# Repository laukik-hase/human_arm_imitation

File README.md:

# Imitation of Human Arm using a 5-DoF Manipulator

<!-- TABLE OF CONTENTS -->

## Table of Contents

- [Imitation of Human Arm using a 5-DoF Manipulator](#imitation-of-human-arm-using-a-5-dof-manipulator)
  - [Table of Contents](#table-of-contents)
  - [About The Project](#about-the-project)
  - [Contributors](#contributors)
  - [Resources](#resources)
  - [Acknowledgements](#acknowledgements)
  - [License](#license)

<!-- ABOUT THE PROJECT -->

## About The Project

- The project aims at develop a 5-DoF manipulator capable of precise imitation of the human arm. The manipulator will be tested in a simulated environment and then implemented in reality.

- The first challenge is to track the position of human joints and acquire joint parameters data.
A motion-capture system consisting of IMU sensors attached to the human arm will be used for the purpose.

- The next challenge is to map the motion of the human to the manipulator, with kinematic and dynamic
modeling of the manipulator for precise and accurate control.

- After establishing a stable system for arm imitation, it will be tested on applications like pick-and-place and tracing a curve.

- Everything about the project: reports, progress, demos (photos and videos) can be found [here](https://drive.google.com/drive/folders/1VRj0Rsg3wywi9sTcepC8vw8A19dxCz2f?usp=sharing).

- For detailed description of the project, view this [report](human_arm_imitation.pdf).

## Contributors

* [Vishnuparammal](https://github.com/Vishnuparammal)
* [ved29](https://github.com/ved29)
* [laukik-hase](https://github.com/laukik-hase)
* [ameya-apte](https://github.com/ameya-apte)

<!-- Acknowledgements and Resources-->

## Resources
- [Concept Development Report](https://drive.google.com/drive/folders/1PC-iJiLeUT0hi6oHv0CTknUYlQUyzkWc?usp=sharing)
- [Progress Status](https://drive.google.com/drive/folders/1OLMFB2oo_8WZqaWDnTHkVBi_Prd8paOJ?usp=sharing)
- [References](https://drive.google.com/drive/folders/1Bxyq7_aq28y-IdtfYdROcifC5CevMQnE?usp=sharing)
## Acknowledgements

- [AVITRA : 2019-2020](https://github.com/SRA-AVITRA)
- [AVITRA : 2018-2019](https://github.com/atharvkhadtare/fyp_ws)
- [AVITRA : 2017-2018](https://github.com/sachin0x18/Imitation)

<!-- LICENSE -->

## License

Distributed under the MIT License. See `LICENSE` for more information.

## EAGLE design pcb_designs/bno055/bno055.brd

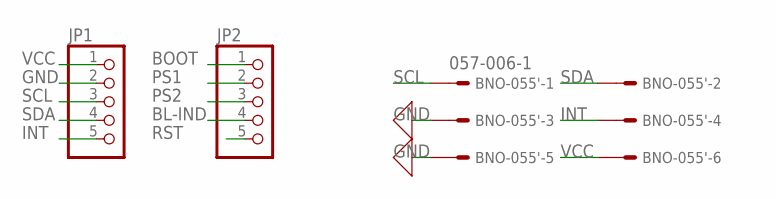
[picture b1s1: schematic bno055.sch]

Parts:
BNO-055': 057-006-1
JP1, JP2: PINHD-1X5; 1X05

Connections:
BL-IND: JP2.4
BOOT: JP2.1
GND: BNO-055'.3, BNO-055'.5, JP1.2
INT: BNO-055'.4, JP1.5
PS1: JP2.2
PS2: JP2.3
RST: JP2.5
SCL: BNO-055'.1, JP1.3
SDA: BNO-055'.2, JP1.4
VCC: BNO-055'.6, JP1.1

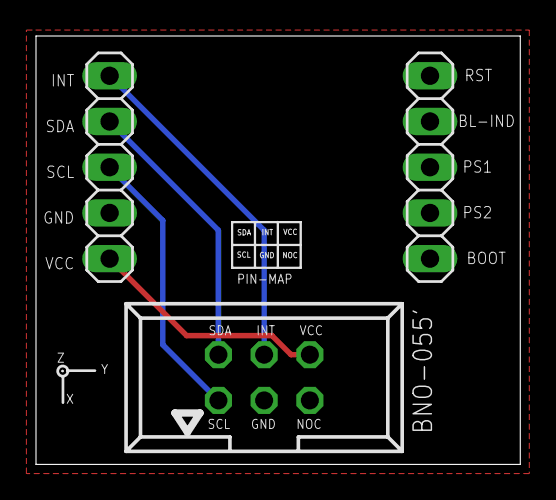
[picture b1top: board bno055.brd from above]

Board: 2 copper layers, 26.9 x 23.8 mm, 3 parts (0 on the bottom side), 5 nets.

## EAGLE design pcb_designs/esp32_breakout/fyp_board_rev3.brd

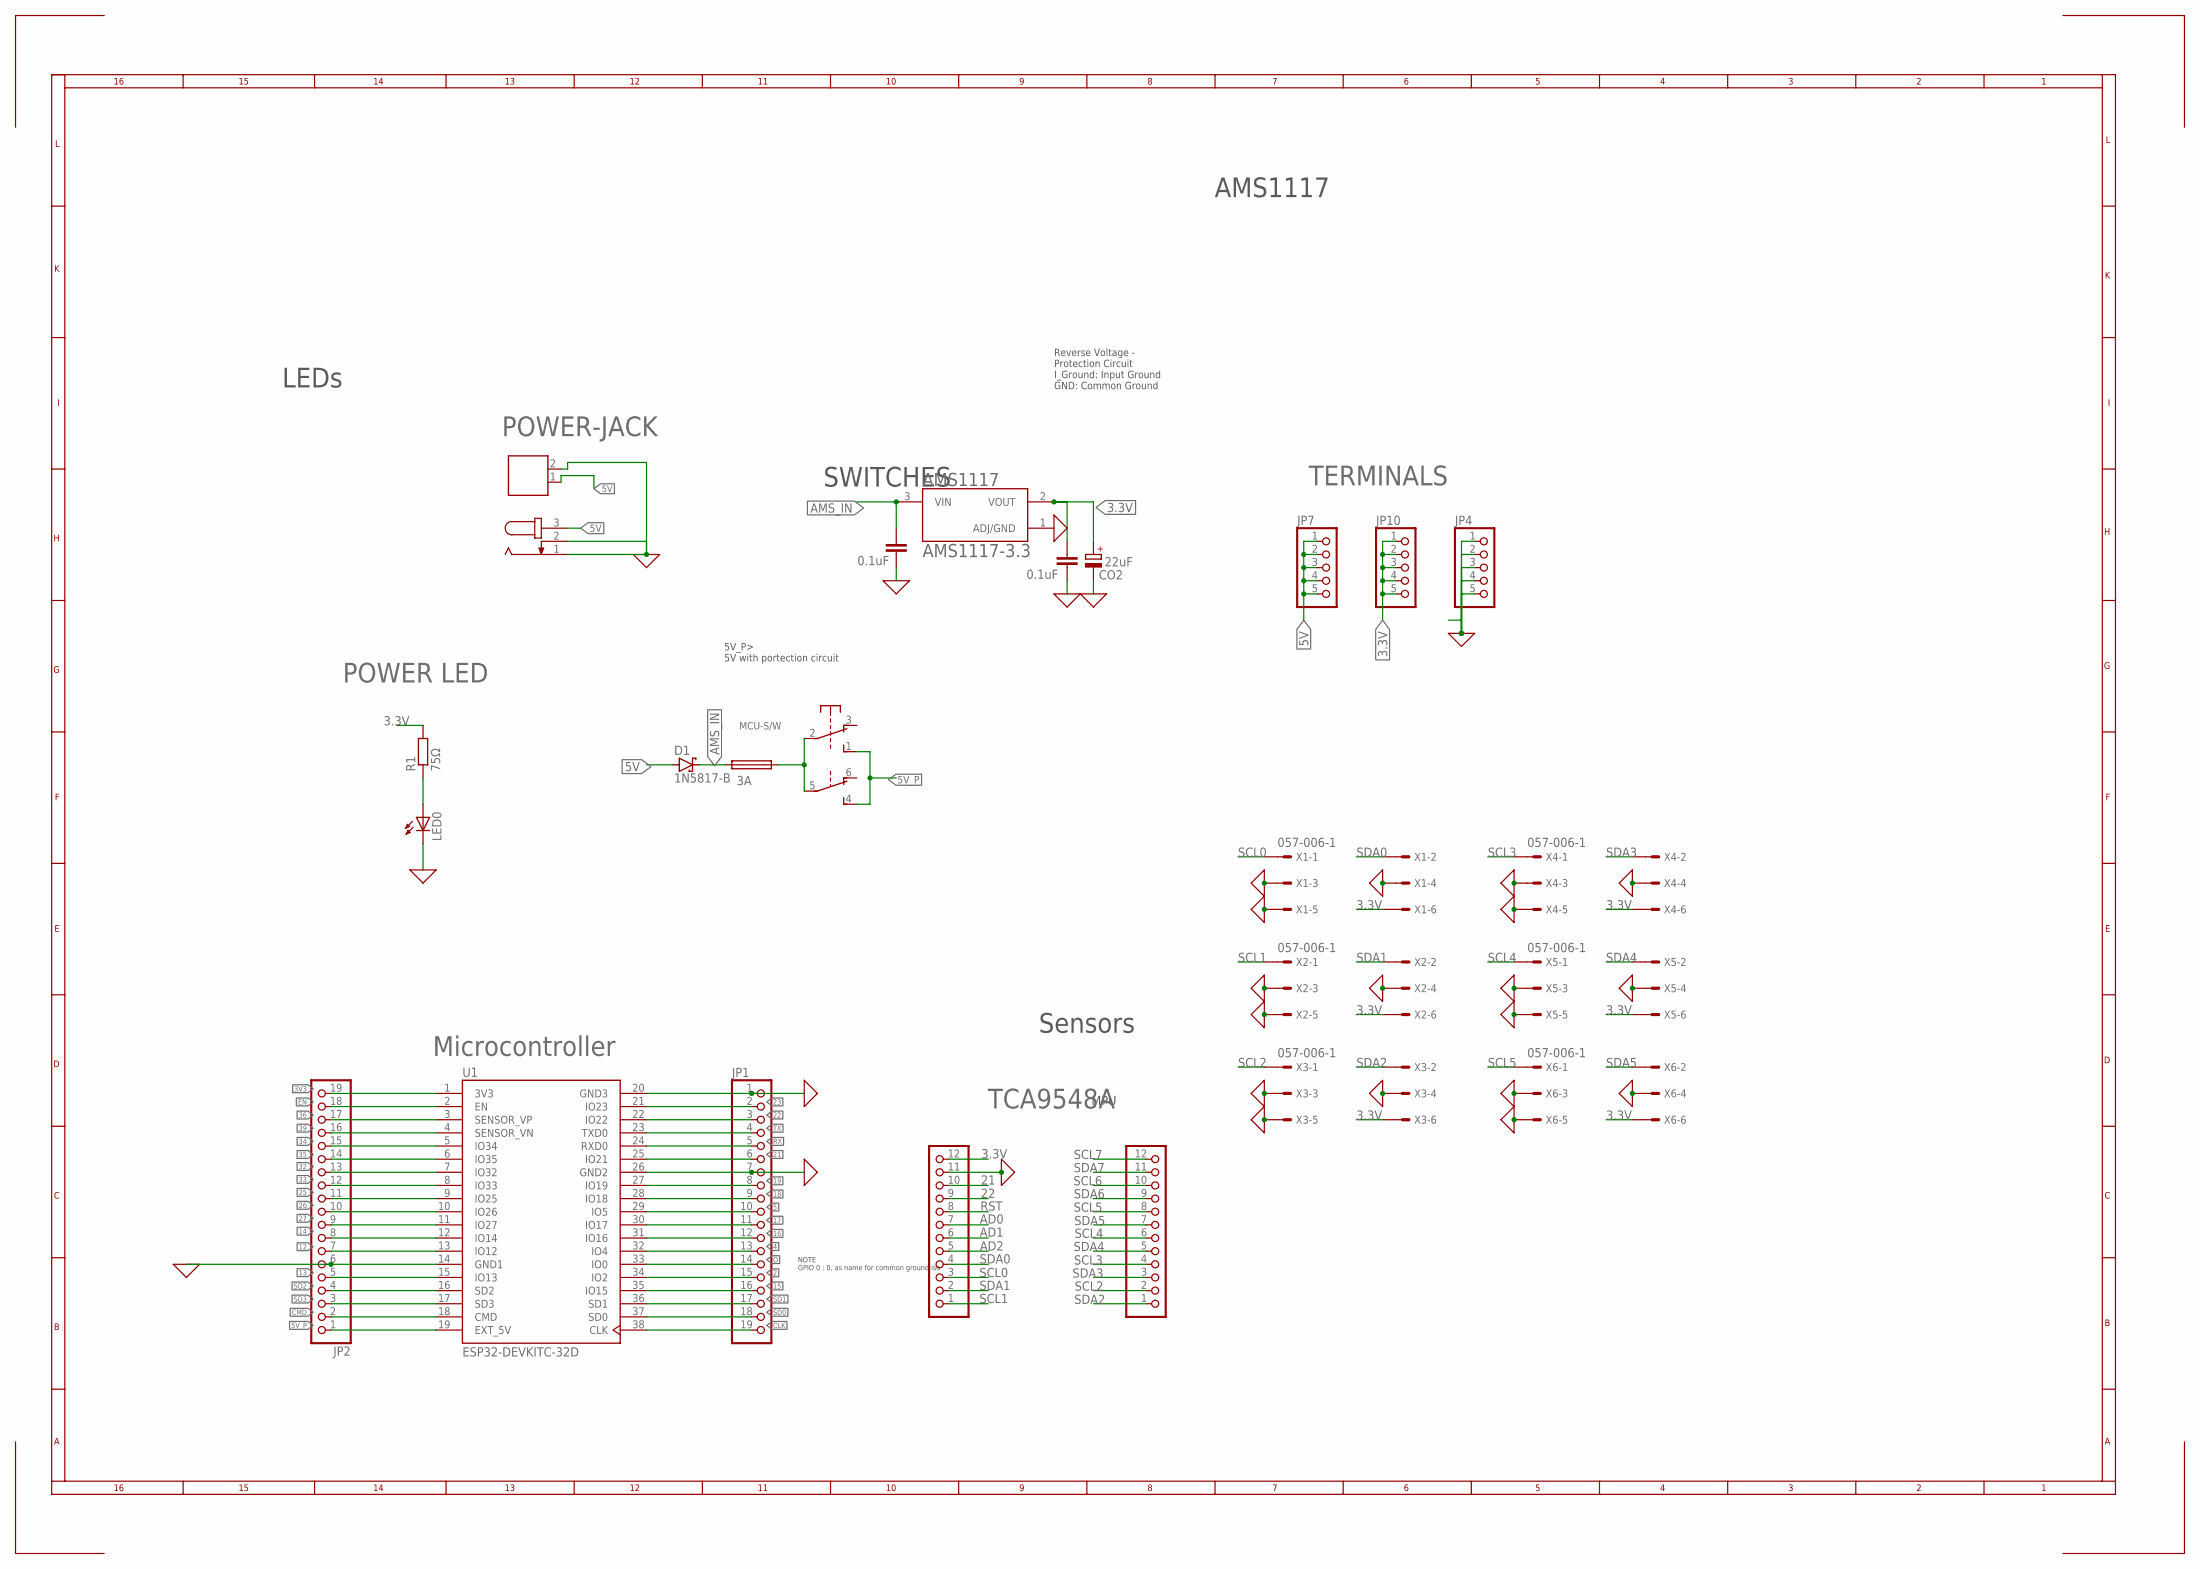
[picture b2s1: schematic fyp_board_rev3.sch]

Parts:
12V: 691131710002
AMS1117: AMS1117-3.3; SOT229P700X180-4N
CIN1: 0.1uF; C5B2.5
CO1: 0.1uF; C5B2.5
CO2: 22uF; E2,5-6
D1: 1N5817-B; DO41-7.6
F2: 3A; SH25
JP1, JP2: PINHD-1X19; 1X19
JP4, JP7, JP10: PINHD-1X5; 1X05
LED0: LED3MM
MCU-S/W: 9077-2
POWER-JACK: JACK-PLUG1; SPC4078
R1: 75Ω; 0207/10
SV2: PINHD-1X12; 1X12
TCA9548: PINHD-1X12; 1X12
U1: ESP32-DEVKITC-32D; MODULE_ESP32-DEVKITC-32D
X1, X2, X3, X4, X5, X6: 057-006-1

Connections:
0: 12V.2, AMS1117.1 (ADJ/GND), CIN1.1, CO1.1, CO2.-, JP1.1, JP1.7, JP2.6, JP4.1, JP4.2, JP4.3, JP4.4, JP4.5, LED0.K (C), POWER-JACK.1, POWER-JACK.2, TCA9548.11, U1.14 (GND1), U1.20 (GND3), U1.26 (GND2), X1.3, X1.4, X1.5, X2.3, X2.4, X2.5, X3.3, X3.4, X3.5, X4.3, X4.4, X4.5, X5.3, X5.4, X5.5, X6.3, X6.4, X6.5
2: JP1.15, U1.34 (IO2)
3.3V: AMS1117.2 (VOUT), CO1.2, CO2.+, JP10.1, JP10.2, JP10.3, JP10.4, JP10.5, R1.2, TCA9548.12, X1.6, X2.6, X3.6, X4.6, X5.6, X6.6
3V3: JP2.19, U1.1 (3V3)
4: JP1.13, U1.32 (IO4)
5: JP1.10, U1.29 (IO5)
5V: 12V.1, D1.A, JP7.1, JP7.2, JP7.3, JP7.4, JP7.5, POWER-JACK.3
5V_P: JP2.1, MCU-S/W.1 (S), MCU-S/W.4 (S), U1.19 (EXT_5V)
5_AF: F2.1, MCU-S/W.2, MCU-S/W.5
12: JP2.7, U1.13 (IO12)
13: JP2.5, U1.15 (IO13)
14: JP2.8, U1.12 (IO14)
15: JP1.16, U1.35 (IO15)
16: JP1.12, U1.31 (IO16)
17: JP1.11, U1.30 (IO17)
18: JP1.9, U1.28 (IO18)
19: JP1.8, U1.27 (IO19)
21: JP1.6, TCA9548.10, U1.25 (IO21)
22: JP1.3, TCA9548.9, U1.22 (IO22)
23: JP1.2, U1.21 (IO23)
25: JP2.11, U1.9 (IO25)
26: JP2.10, U1.10 (IO26)
27: JP2.9, U1.11 (IO27)
32: JP2.13, U1.7 (IO32)
33: JP2.12, U1.8 (IO33)
34: JP2.15, U1.5 (IO34)
35: JP2.14, U1.6 (IO35)
36: JP2.17, U1.3 (SENSOR_VP)
39: JP2.16, U1.4 (SENSOR_VN)
AD0: TCA9548.7
AD1: TCA9548.6
AD2: TCA9548.5
AMS_IN: AMS1117.3 (VIN), CIN1.2, D1.C, F2.2
CLK: JP1.19, U1.38 (CLK)
CMD: JP2.2, U1.18 (CMD)
EN: JP2.18, U1.2 (EN)
unnamed: LED0.A, R1.1
O: JP1.14, U1.33 (IO0)
RST: TCA9548.8
RX: JP1.5, U1.24 (RXD0)
SCL0: TCA9548.3, X1.1
SCL1: TCA9548.1, X2.1
SCL2: SV2.2, X3.1
SCL3: SV2.4, X4.1
SCL4: SV2.6, X5.1
SCL5: SV2.8, X6.1
SCL6: SV2.10
SCL7: SV2.12
SD0: JP1.18, U1.37 (SD0)
SD1: JP1.17, U1.36 (SD1)
SD2: JP2.4, U1.16 (SD2)
SD3: JP2.3, U1.17 (SD3)
SDA0: TCA9548.4, X1.2
SDA1: TCA9548.2, X2.2
SDA2: SV2.1, X3.2
SDA3: SV2.3, X4.2
SDA4: SV2.5, X5.2
SDA5: SV2.7, X6.2
SDA6: SV2.9
SDA7: SV2.11
TX: JP1.4, U1.23 (TXD0)

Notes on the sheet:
TERMINALS
Microcontroller
Reverse Voltage - Protection Circuit I_Ground: Input Ground GND: Common Ground
SWITCHES
5V_P> 5V with portection circuit
Sensors
MPU
NOTE GPIO 0 : 0, as name for common ground iso
AMS1117
LEDs
TCA9548A
POWER LED

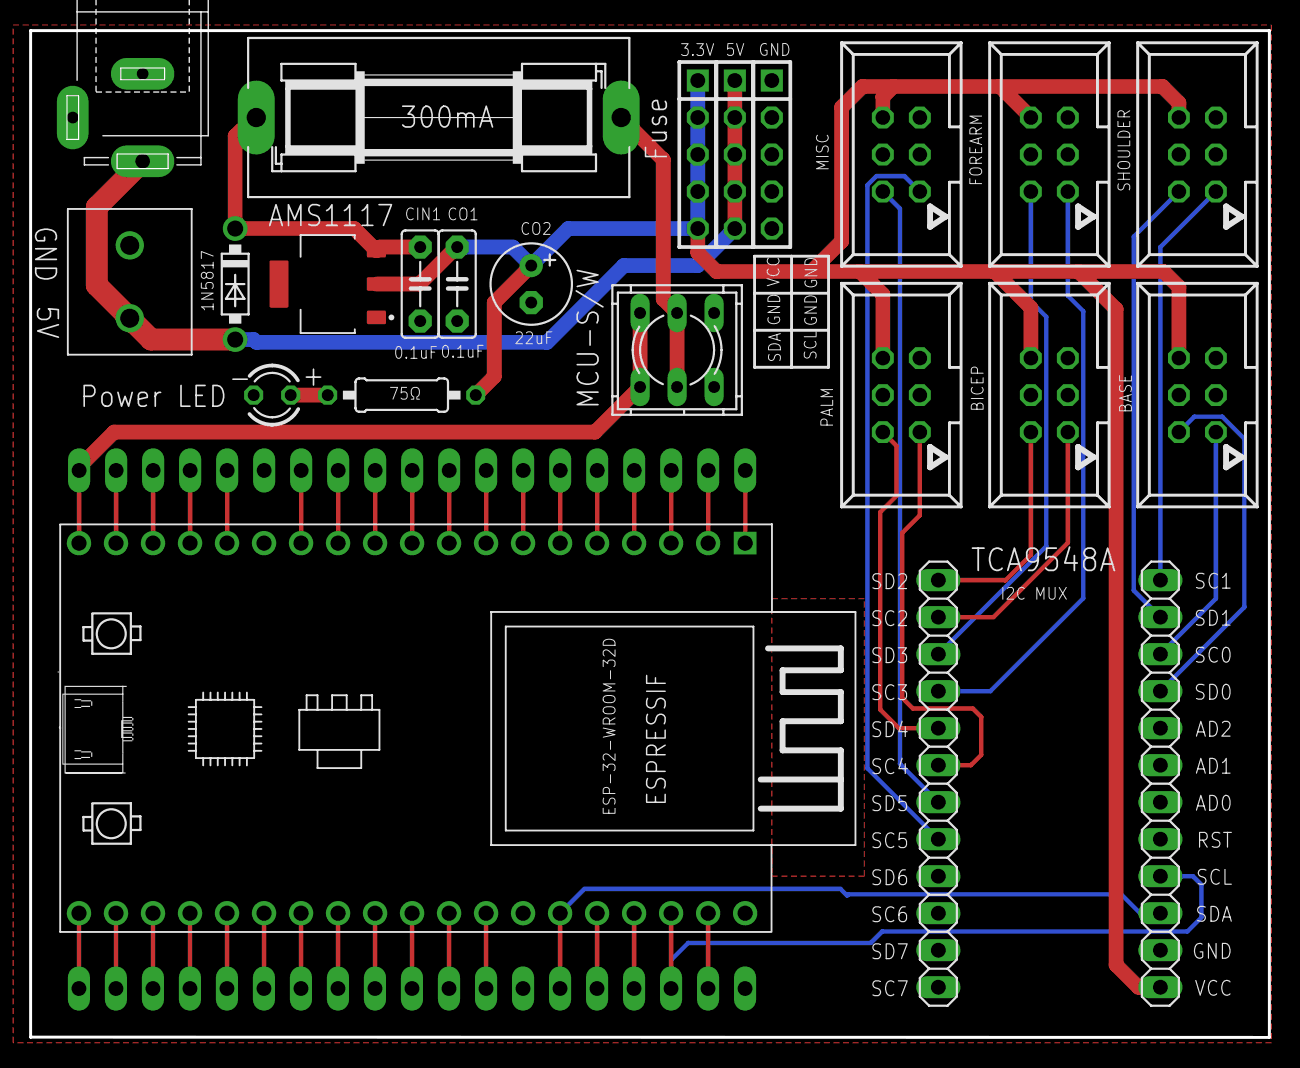
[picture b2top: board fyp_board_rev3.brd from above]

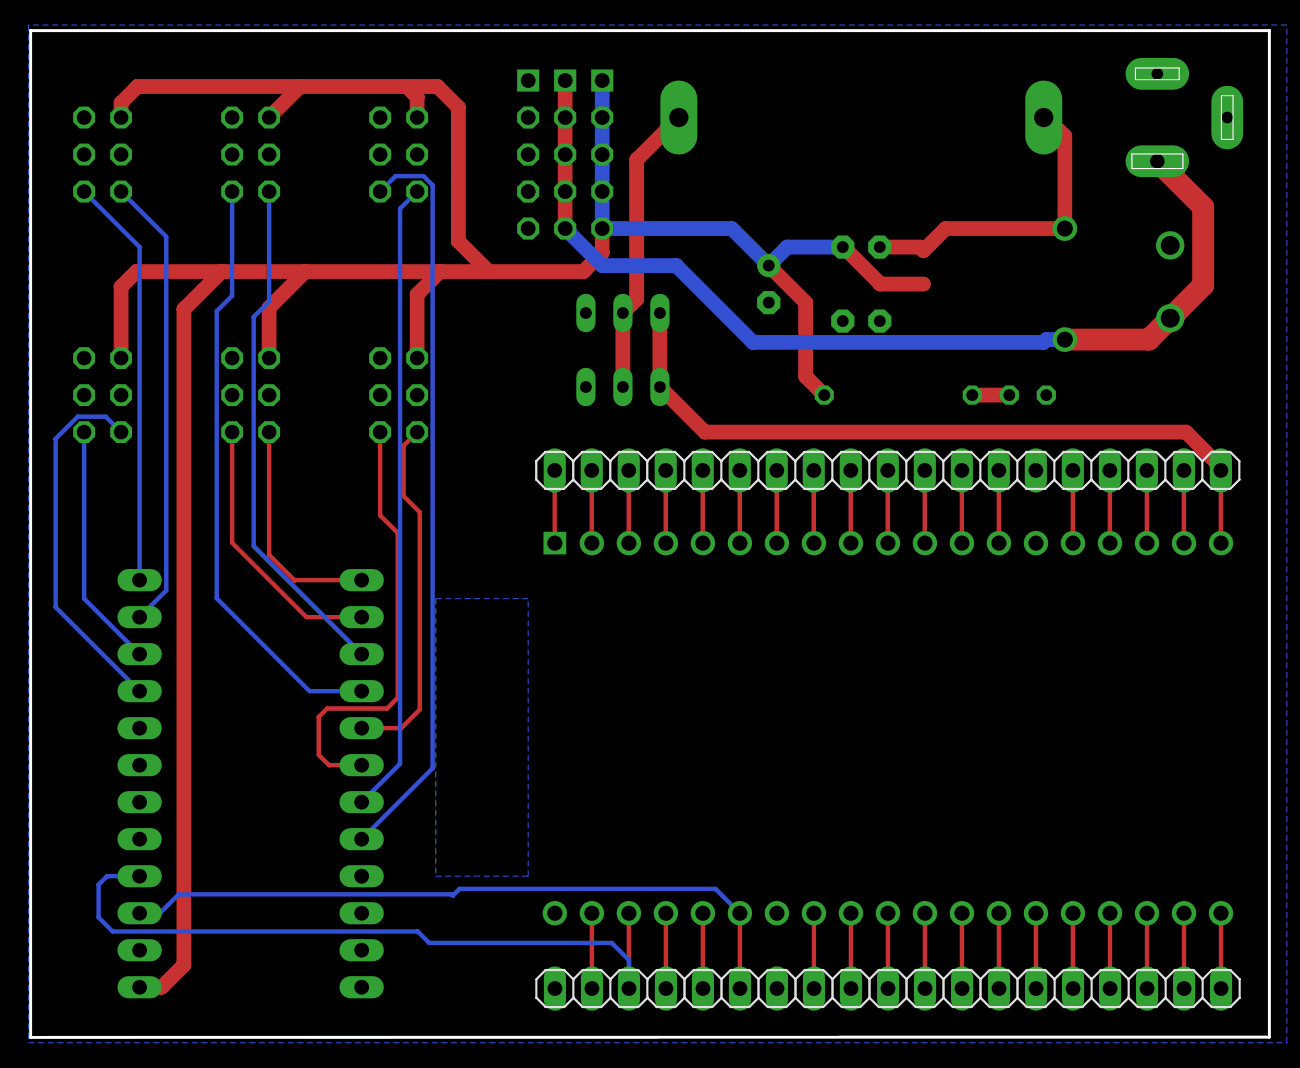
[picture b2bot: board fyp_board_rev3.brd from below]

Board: 2 copper layers, 85.0 x 69.1 mm, 25 parts (2 on the bottom side), 53 nets.

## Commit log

2020-08-21 Setting up README
2020-08-22 README updated wth resources
2020-08-23 Create LICENSE
2020-09-08 added ros package for arm control on coppeliasim
2020-09-11 Extraction of link roll and pitch angles
2020-09-13 rbdl verified without forces
2020-09-14 Joint angle - pitch and roll span calculated 1) Added multiple datasets 2) Fixed gyro raw data to angle conversion
2020-09-14 position controlled imitation complete
2020-12-10 Added ESP32 - MPU9250 files - extracted roll, pitch, yaw
2020-12-11 imitation on hardware arm
2021-01-22 Joint IMU Angle Extraction using Madgwick Filter 1) Extracted joint angles with low noise 2) Added PCB designs for controller board and IMU breakout
2021-03-25 dynaban tests with pypot motor control
2021-04-06 routine commit
2021-04-08 Added BNO055 MPU files
2021-04-08 Fix bno055 link error
2021-04-08 Removing BNO055 files
2021-04-08 Added BNO055 files
2021-04-10 Interpolation for positioncontrol
2021-04-10 Interpolation for multi motor position control
2021-04-10 Interpolation for multi motor position control with single csv read
2021-04-10 Degree 5 polynomial interpolation for multi motor position control
2021-04-10 Adding edited csv file
2021-04-11 Adding csv for comparing torque values
2021-04-12 Final interpolation code for multi motor position control
2021-04-14 Interpolation final edited code for multi motor position control
2021-04-16 Interpolation with moving average values for multi motor position control
2021-04-17 cleaned up curve calculation code
2021-04-17 cleaned manipulator_math_utils.py
2021-04-18 Extracted 4 joint angles successfully 1) Corrected yaw joint angle calculation 2) Added calibration example with offsets stored to NVS
2021-04-20 Adding csv files for copsim circle motion
2021-04-20 Adding csv files for all joints copsim circle motion
2021-04-20 Final circle motion csv data
2021-04-21 circular motion complete
2021-05-01 Old Commit
2021-05-02 csv files relocated
2021-05-02 Mqtt Codes
2021-05-03 Added Feature: MQTT 1) Sent joint angles over MQTT in JSON packets 2) Added WiFi and Mqtt utility functions
2021-05-03 Added Feature: Gripper control with GPIO 1) Gripper control with GPIO using ISR 2) Heading towards the end-goal -> sending timestamps, joint angles and gripper state over MQTT
2021-05-03 real_time_manipulator_utils
2021-05-06 urdf with gripper complete
2021-05-08 qos test changes
2021-05-08 subscribe unsubscribe toggle
2021-05-12 real time imitation
2021-06-11 added drawing circle in coppeliasim
2021-11-13 Restructured files for better viewing

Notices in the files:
parts and their libraries:
Wurth_Elektronik_Electromechanic_Termina: Copyright: Würth Elektronik
